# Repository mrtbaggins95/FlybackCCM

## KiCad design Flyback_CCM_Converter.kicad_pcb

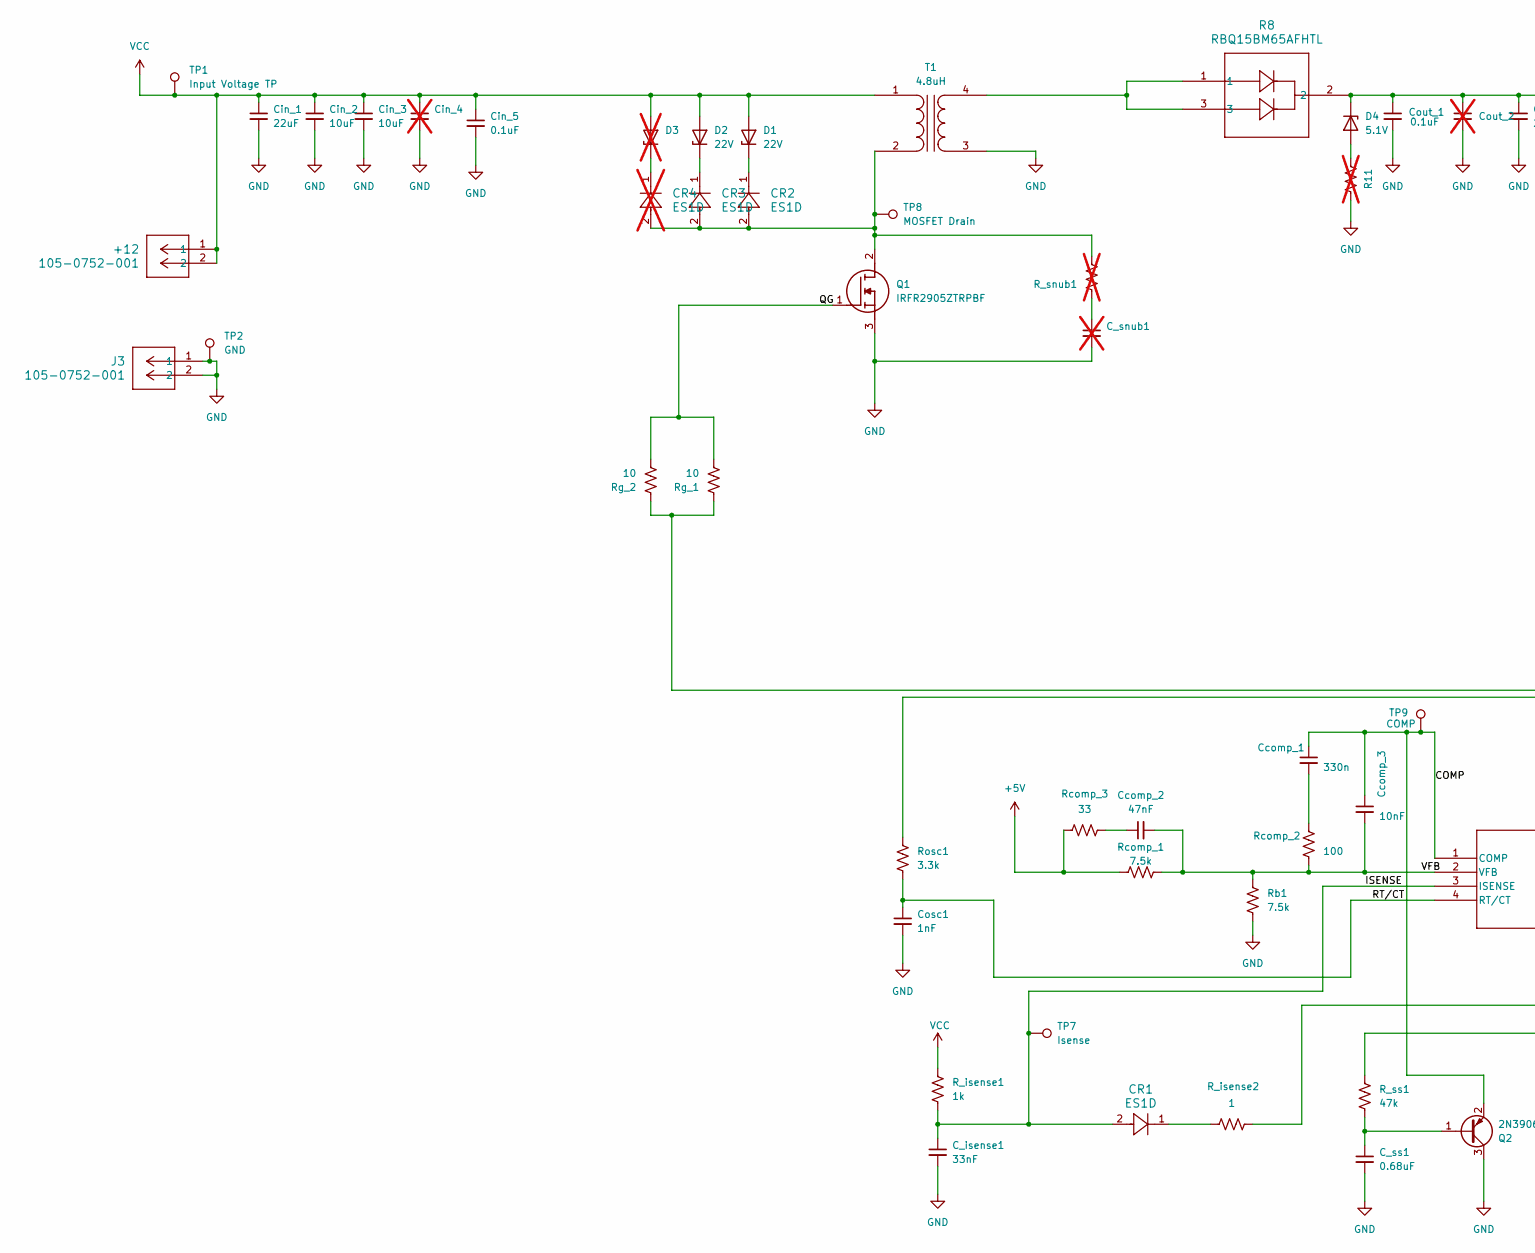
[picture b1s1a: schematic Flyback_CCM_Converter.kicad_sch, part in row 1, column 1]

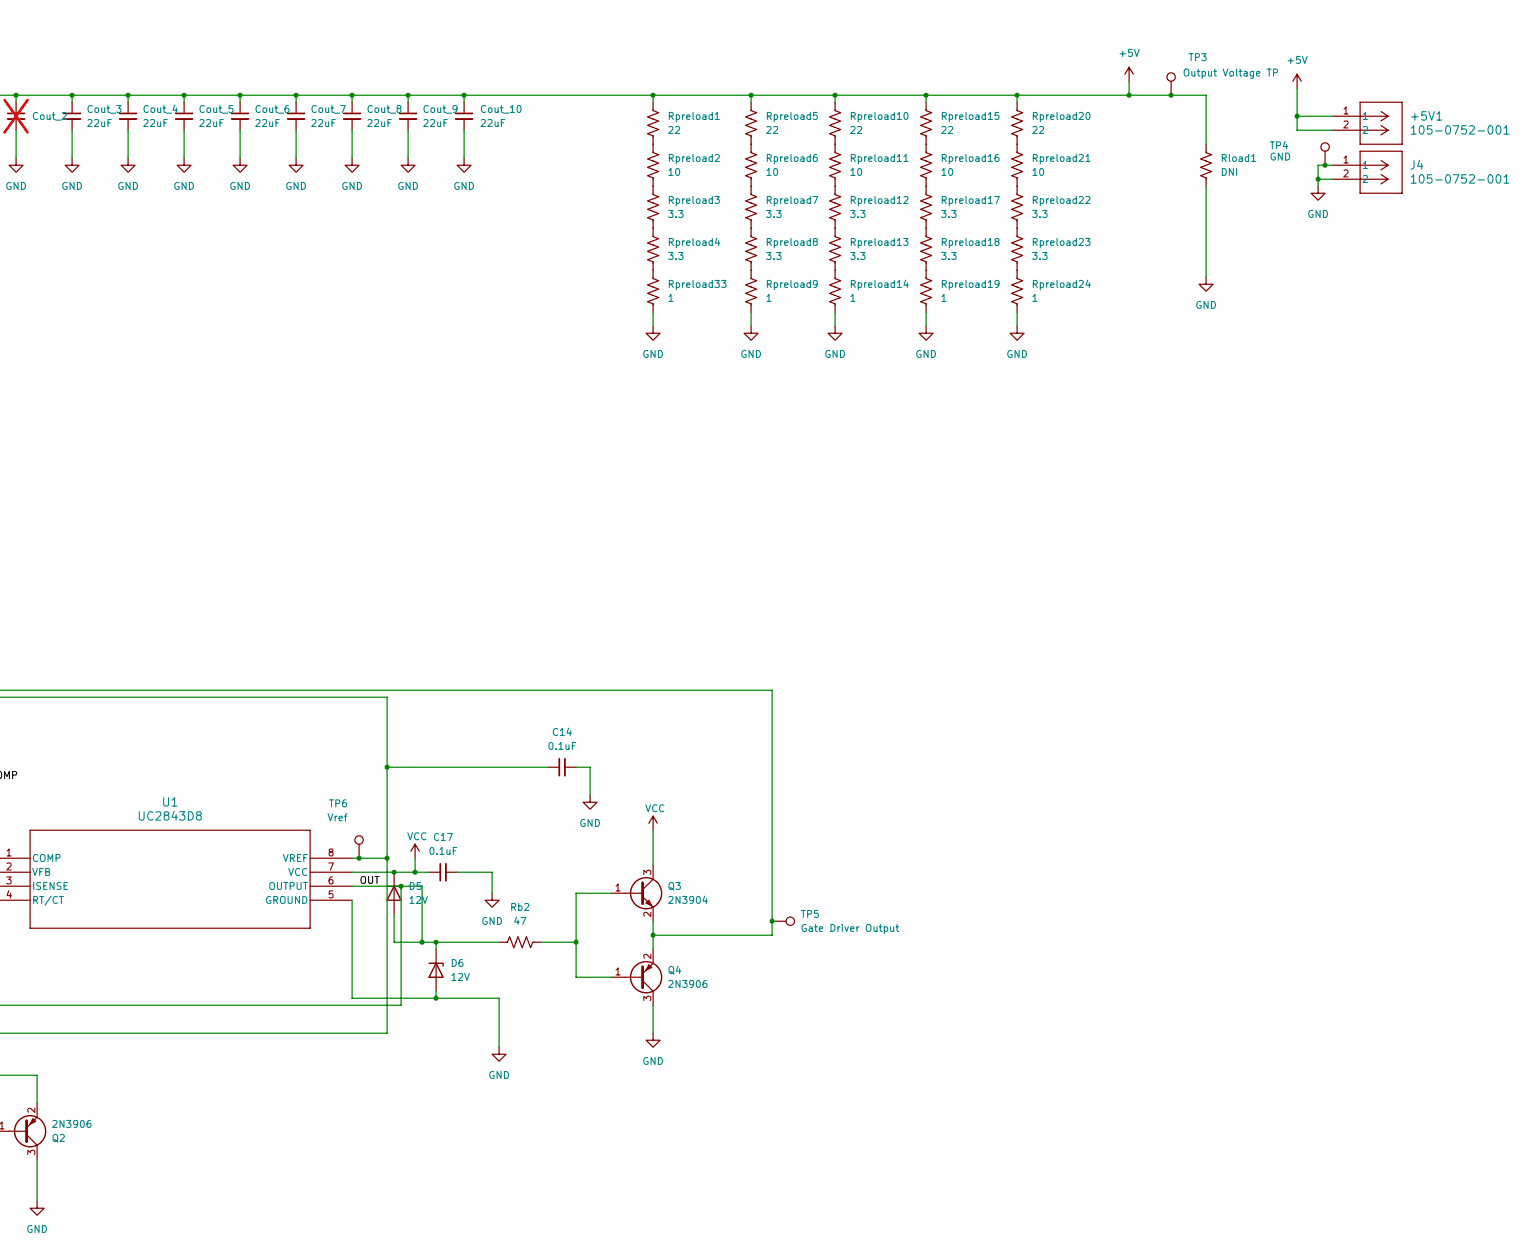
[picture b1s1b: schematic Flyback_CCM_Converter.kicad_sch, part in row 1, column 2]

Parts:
+5V1, +12: 105-0752-001; CONN_0752-001
C14: 0.1uF; C_0603_1608Metric_Pad1.08x0.95mm_HandSolder
C17: 0.1uF; C_1206_3216Metric_Pad1.33x1.80mm_HandSolder
CR1, CR2, CR3: ES1D
CR4: ES1D; not fitted
C_isense1: 33nF; C_1206_3216Metric_Pad1.33x1.80mm_HandSolder
C_snub1: C_1206_3216Metric_Pad1.33x1.80mm_HandSolder; not fitted
C_ss1: 0.68uF; C_0805_2012Metric_Pad1.18x1.45mm_HandSolder
Ccomp_1: 330n; C_1206_3216Metric_Pad1.33x1.80mm_HandSolder
Ccomp_2: 47nF; C_1206_3216Metric_Pad1.33x1.80mm_HandSolder
Ccomp_3: 10nF; C_1206_3216Metric_Pad1.33x1.80mm_HandSolder
Cin_1: 22uF; C_1206_3216Metric_Pad1.33x1.80mm_HandSolder
Cin_2, Cin_3: 10uF; C_1206_3216Metric_Pad1.33x1.80mm_HandSolder
Cin_4: C_1206_3216Metric_Pad1.33x1.80mm_HandSolder; not fitted
Cin_5: 0.1uF; C_1206_3216Metric_Pad1.33x1.80mm_HandSolder
Cosc1: 1nF; C_1206_3216Metric_Pad1.33x1.80mm_HandSolder
Cout_1: 0.1uF; C_1206_3216Metric_Pad1.33x1.80mm_HandSolder
Cout_2: C_1206_3216Metric_Pad1.33x1.80mm_HandSolder; not fitted
Cout_3, Cout_4, Cout_5, Cout_6, Cout_7, Cout_8, Cout_9, Cout_10: 22uF; C_1206_3216Metric_Pad1.33x1.80mm_HandSolder
D1, D2: 22V; D_MiniMELF_Handsoldering
D3: D_MiniMELF_Handsoldering; not fitted
D4: 5.1V; D_MiniMELF_Handsoldering
D5, D6: 12V; D_MiniMELF_Handsoldering
J3, J4: 105-0752-001; CONN_0752-001
Q1: IRFR2905ZTRPBF; Manufacturer_Part_Number IRFR2905ZTRPBF
Q2: 2N3906; TSOT-23
Q3: 2N3904; TSOT-23_HandSoldering
Q4: 2N3906; TSOT-23_HandSoldering
R8: RBQ15BM65AFHTL; TO-252-2
R11: R_1206_3216Metric_Pad1.30x1.75mm_HandSolder; not fitted
R_isense1: 1k; R_1206_3216Metric_Pad1.30x1.75mm_HandSolder
R_isense2: 1; R_1206_3216Metric_Pad1.30x1.75mm_HandSolder
R_snub1: R_1206_3216Metric_Pad1.30x1.75mm_HandSolder; not fitted
R_ss1: 47k; R_1206_3216Metric_Pad1.30x1.75mm_HandSolder
Rb1: 7.5k; R_1206_3216Metric_Pad1.30x1.75mm_HandSolder
Rb2: 47; R_0805_2012Metric_Pad1.20x1.40mm_HandSolder
Rcomp_1: 7.5k; R_0603_1608Metric_Pad0.98x0.95mm_HandSolder
Rcomp_2: 100; R_0603_1608Metric_Pad0.98x0.95mm_HandSolder
Rcomp_3: 33; R_0603_1608Metric_Pad0.98x0.95mm_HandSolder
Rg_1, Rg_2: 10; R_1206_3216Metric_Pad1.30x1.75mm_HandSolder
Rload1: DNI; R_1206_3216Metric_Pad1.30x1.75mm_HandSolder
Rosc1: 3.3k; R_1206_3216Metric_Pad1.30x1.75mm_HandSolder
Rpreload1, Rpreload5, Rpreload10, Rpreload15, Rpreload20: 22; R_1206_3216Metric_Pad1.30x1.75mm_HandSolder
Rpreload2, Rpreload6, Rpreload11, Rpreload16, Rpreload21: 10; R_1206_3216Metric_Pad1.30x1.75mm_HandSolder
Rpreload3, Rpreload4, Rpreload7, Rpreload8, Rpreload12, Rpreload13, Rpreload17, Rpreload18, Rpreload22, Rpreload23: 3.3; R_1206_3216Metric_Pad1.30x1.75mm_HandSolder
Rpreload9, Rpreload14, Rpreload19, Rpreload24, Rpreload33: 1; R_1206_3216Metric_Pad1.30x1.75mm_HandSolder
T1: 4.8uH; Flyback_Xfmr
TP1: Input Voltage TP; TestPoint_THTPad_2.0x2.0mm_Drill1.0mm
TP2, TP4: GND; TestPoint_THTPad_2.0x2.0mm_Drill1.0mm
TP3: Output Voltage TP; TestPoint_THTPad_2.0x2.0mm_Drill1.0mm
TP5: Gate Driver Output; TestPoint_THTPad_2.0x2.0mm_Drill1.0mm
TP6: Vref; TestPoint_THTPad_2.0x2.0mm_Drill1.0mm
TP7: Isense; TestPoint_THTPad_2.0x2.0mm_Drill1.0mm
TP8: MOSFET Drain; TestPoint_THTPad_2.0x2.0mm_Drill1.0mm
TP9: COMP; TestPoint_THTPad_2.0x2.0mm_Drill1.0mm
U1: UC2843D8

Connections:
+5V: +5V1.1, +5V1.2, Cout_1.1, Cout_2.1, Cout_3.1, Cout_4.1, Cout_5.1, Cout_6.1, Cout_7.1, Cout_8.1, Cout_9.1, Cout_10.1, D4.1 (K), R8.2, Rcomp_1.2, Rcomp_3.1, Rload1.1, Rpreload1.1, Rpreload5.1, Rpreload10.1, Rpreload15.1, Rpreload20.1, TP3.1
/COMP: Ccomp_1.1, Ccomp_3.1, Q2.2 (E), TP9.1, U1.1 (COMP)
/ISENSE: CR1.2, C_isense1.1, R_isense1.1, TP7.1, U1.3 (ISENSE)
/OUT: D5.2 (A), D6.1 (K), R_isense2.2, Rb2.1, U1.6 (OUTPUT)
/QG: Q1.1 (G), Rg_1.2, Rg_2.2
/RT/CT: Cosc1.1, Rosc1.1, U1.4 (RT/CT)
/VFB: Ccomp_2.2, Ccomp_3.2, Rb1.2, Rcomp_1.1, Rcomp_2.1, U1.2 (VFB)
GND: C14.2, C17.2, C_isense1.2, C_snub1.2, C_ss1.2, Cin_1.2, Cin_2.2, Cin_3.2, Cin_4.2, Cin_5.2, Cosc1.2, Cout_1.2, Cout_2.2, Cout_3.2, Cout_4.2, Cout_5.2, Cout_6.2, Cout_7.2, Cout_8.2, Cout_9.2, Cout_10.2, D6.2 (A), J3.1, J3.2, J4.1, J4.2, Q1.3 (S), Q2.3 (C), Q4.3 (C), R11.1, Rb1.1, Rload1.2, Rpreload9.2, Rpreload14.2, Rpreload19.2, Rpreload24.2, Rpreload33.2, T1.3 (SA), TP2.1, TP4.1, U1.5 (GROUND)
unnamed: CR1.1, R_isense2.1
unnamed: C_snub1.1, R_snub1.1
unnamed: Ccomp_1.2, Rcomp_2.2
unnamed: Ccomp_2.1, Rcomp_3.2
unnamed: CR2.1, D1.1 (K)
unnamed: CR3.1, D2.1 (K)
unnamed: CR4.1, D3.1 (K)
unnamed: D4.2 (A), R11.2
unnamed: CR2.2, CR3.2, CR4.2, Q1.2 (D), R_snub1.2, T1.2 (AB), TP8.1
unnamed: C_ss1.1, Q2.1 (B), R_ss1.1
unnamed: Q3.1 (B), Q4.1 (B), Rb2.2
unnamed: Q3.2 (E), Q4.2 (E), Rg_1.1, Rg_2.1, TP5.1
unnamed: Rpreload1.2, Rpreload2.1
unnamed: Rpreload2.2, Rpreload3.1
unnamed: Rpreload3.2, Rpreload4.1
unnamed: Rpreload5.2, Rpreload6.1
unnamed: Rpreload6.2, Rpreload7.1
unnamed: Rpreload7.2, Rpreload8.1
unnamed: Rpreload8.2, Rpreload9.1
unnamed: Rpreload10.2, Rpreload11.1
unnamed: Rpreload11.2, Rpreload12.1
unnamed: Rpreload12.2, Rpreload13.1
unnamed: Rpreload13.2, Rpreload14.1
unnamed: Rpreload15.2, Rpreload16.1
unnamed: Rpreload16.2, Rpreload17.1
unnamed: Rpreload17.2, Rpreload18.1
unnamed: Rpreload18.2, Rpreload19.1
unnamed: Rpreload20.2, Rpreload21.1
unnamed: Rpreload21.2, Rpreload22.1
unnamed: Rpreload22.2, Rpreload23.1
unnamed: Rpreload23.2, Rpreload24.1
unnamed: Rpreload4.2, Rpreload33.1
unnamed: R8.1, R8.3, T1.4 (SB)
unnamed: C14.1, R_ss1.2, Rosc1.2, TP6.1, U1.8 (VREF)
VCC: +12.1, +12.2, C17.1, Cin_1.1, Cin_2.1, Cin_3.1, Cin_4.1, Cin_5.1, D1.2 (A), D2.2 (A), D3.2 (A), D5.1 (K), Q3.3 (C), R_isense1.2, T1.1 (AA), TP1.1, U1.7 (VCC)

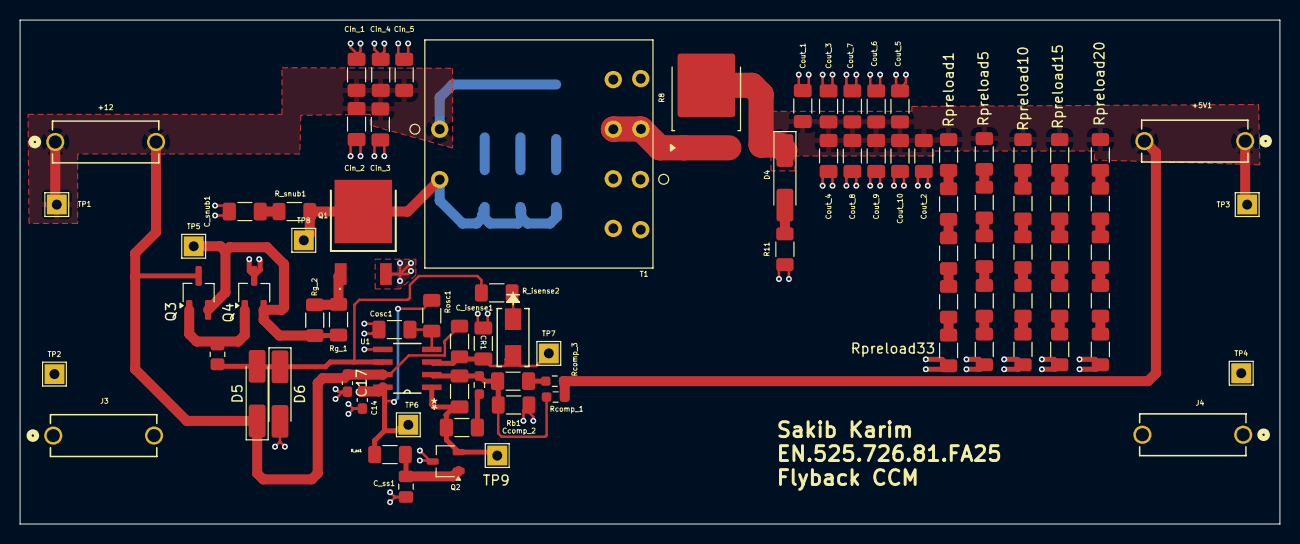
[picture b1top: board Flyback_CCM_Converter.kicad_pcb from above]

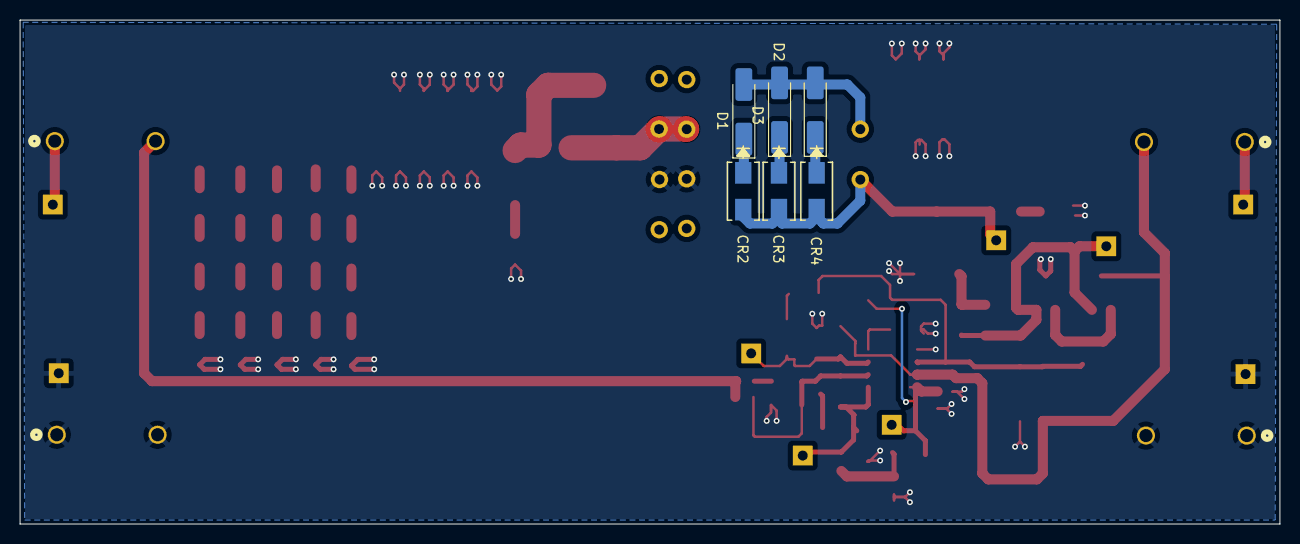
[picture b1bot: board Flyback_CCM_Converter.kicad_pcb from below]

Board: 2 copper layers, 127.0 x 50.8 mm, 92 parts (6 on the bottom side), 43 nets.
